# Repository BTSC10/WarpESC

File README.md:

# WarpESC
An open source 2 channel 50A ESC designed for a 2-4S LiPo Battery.
The design utilises a STM32F303 and 6 SIC634CD-T1-GE3 power stages to produce the 3 phase voltages.

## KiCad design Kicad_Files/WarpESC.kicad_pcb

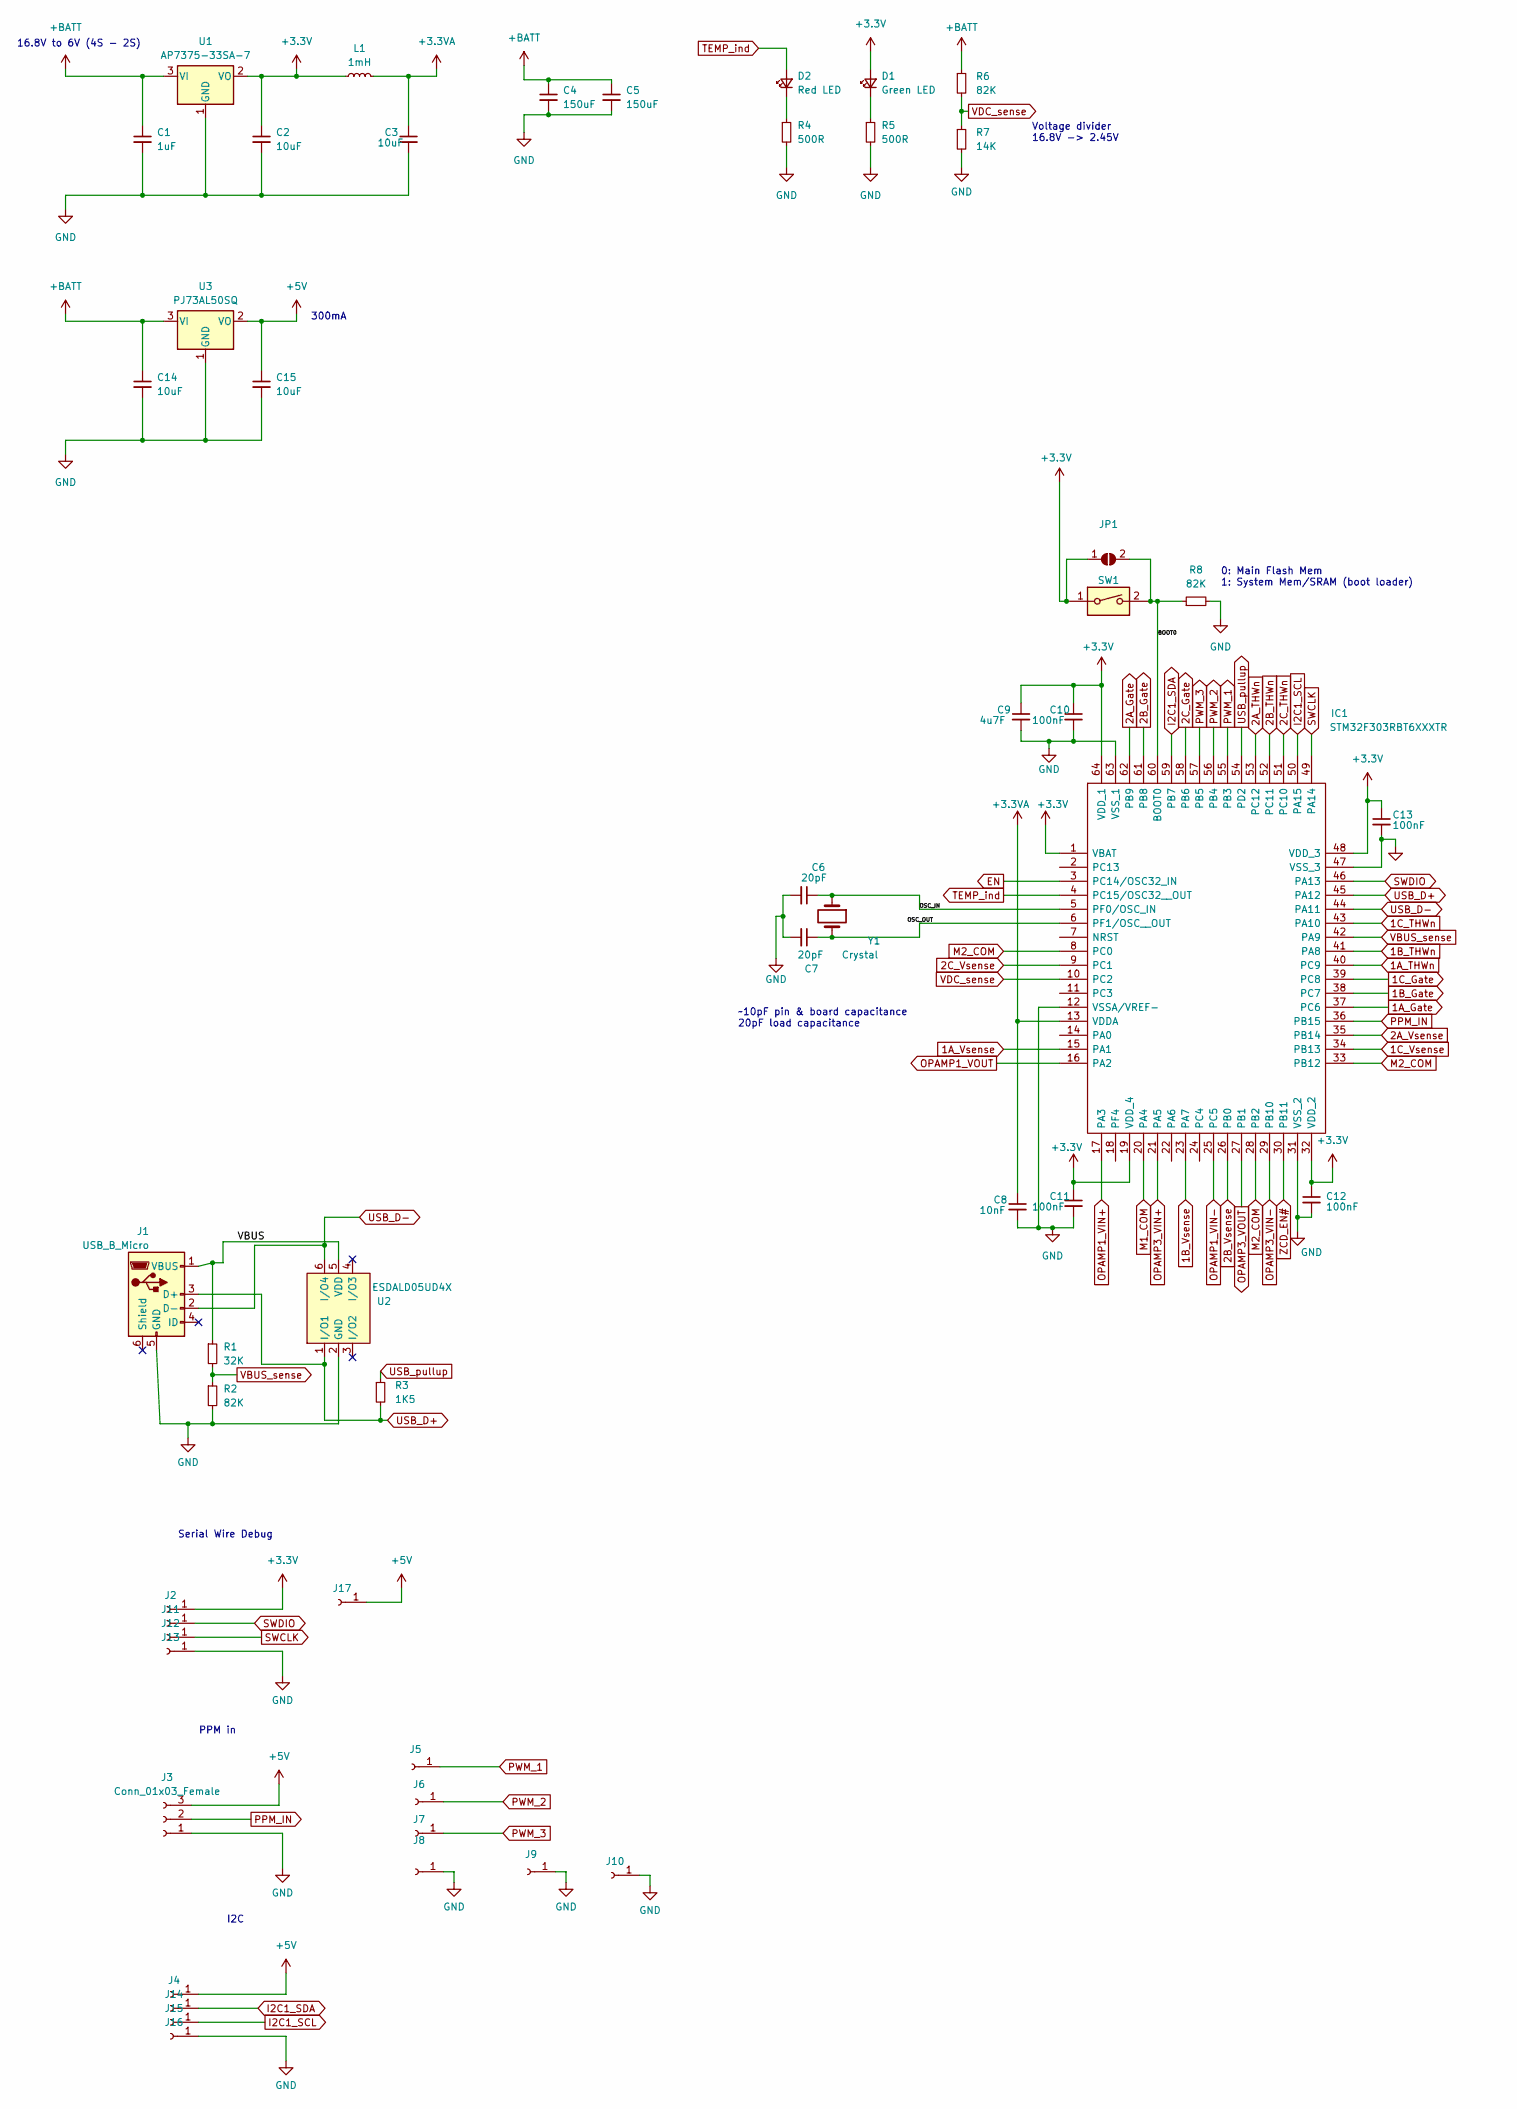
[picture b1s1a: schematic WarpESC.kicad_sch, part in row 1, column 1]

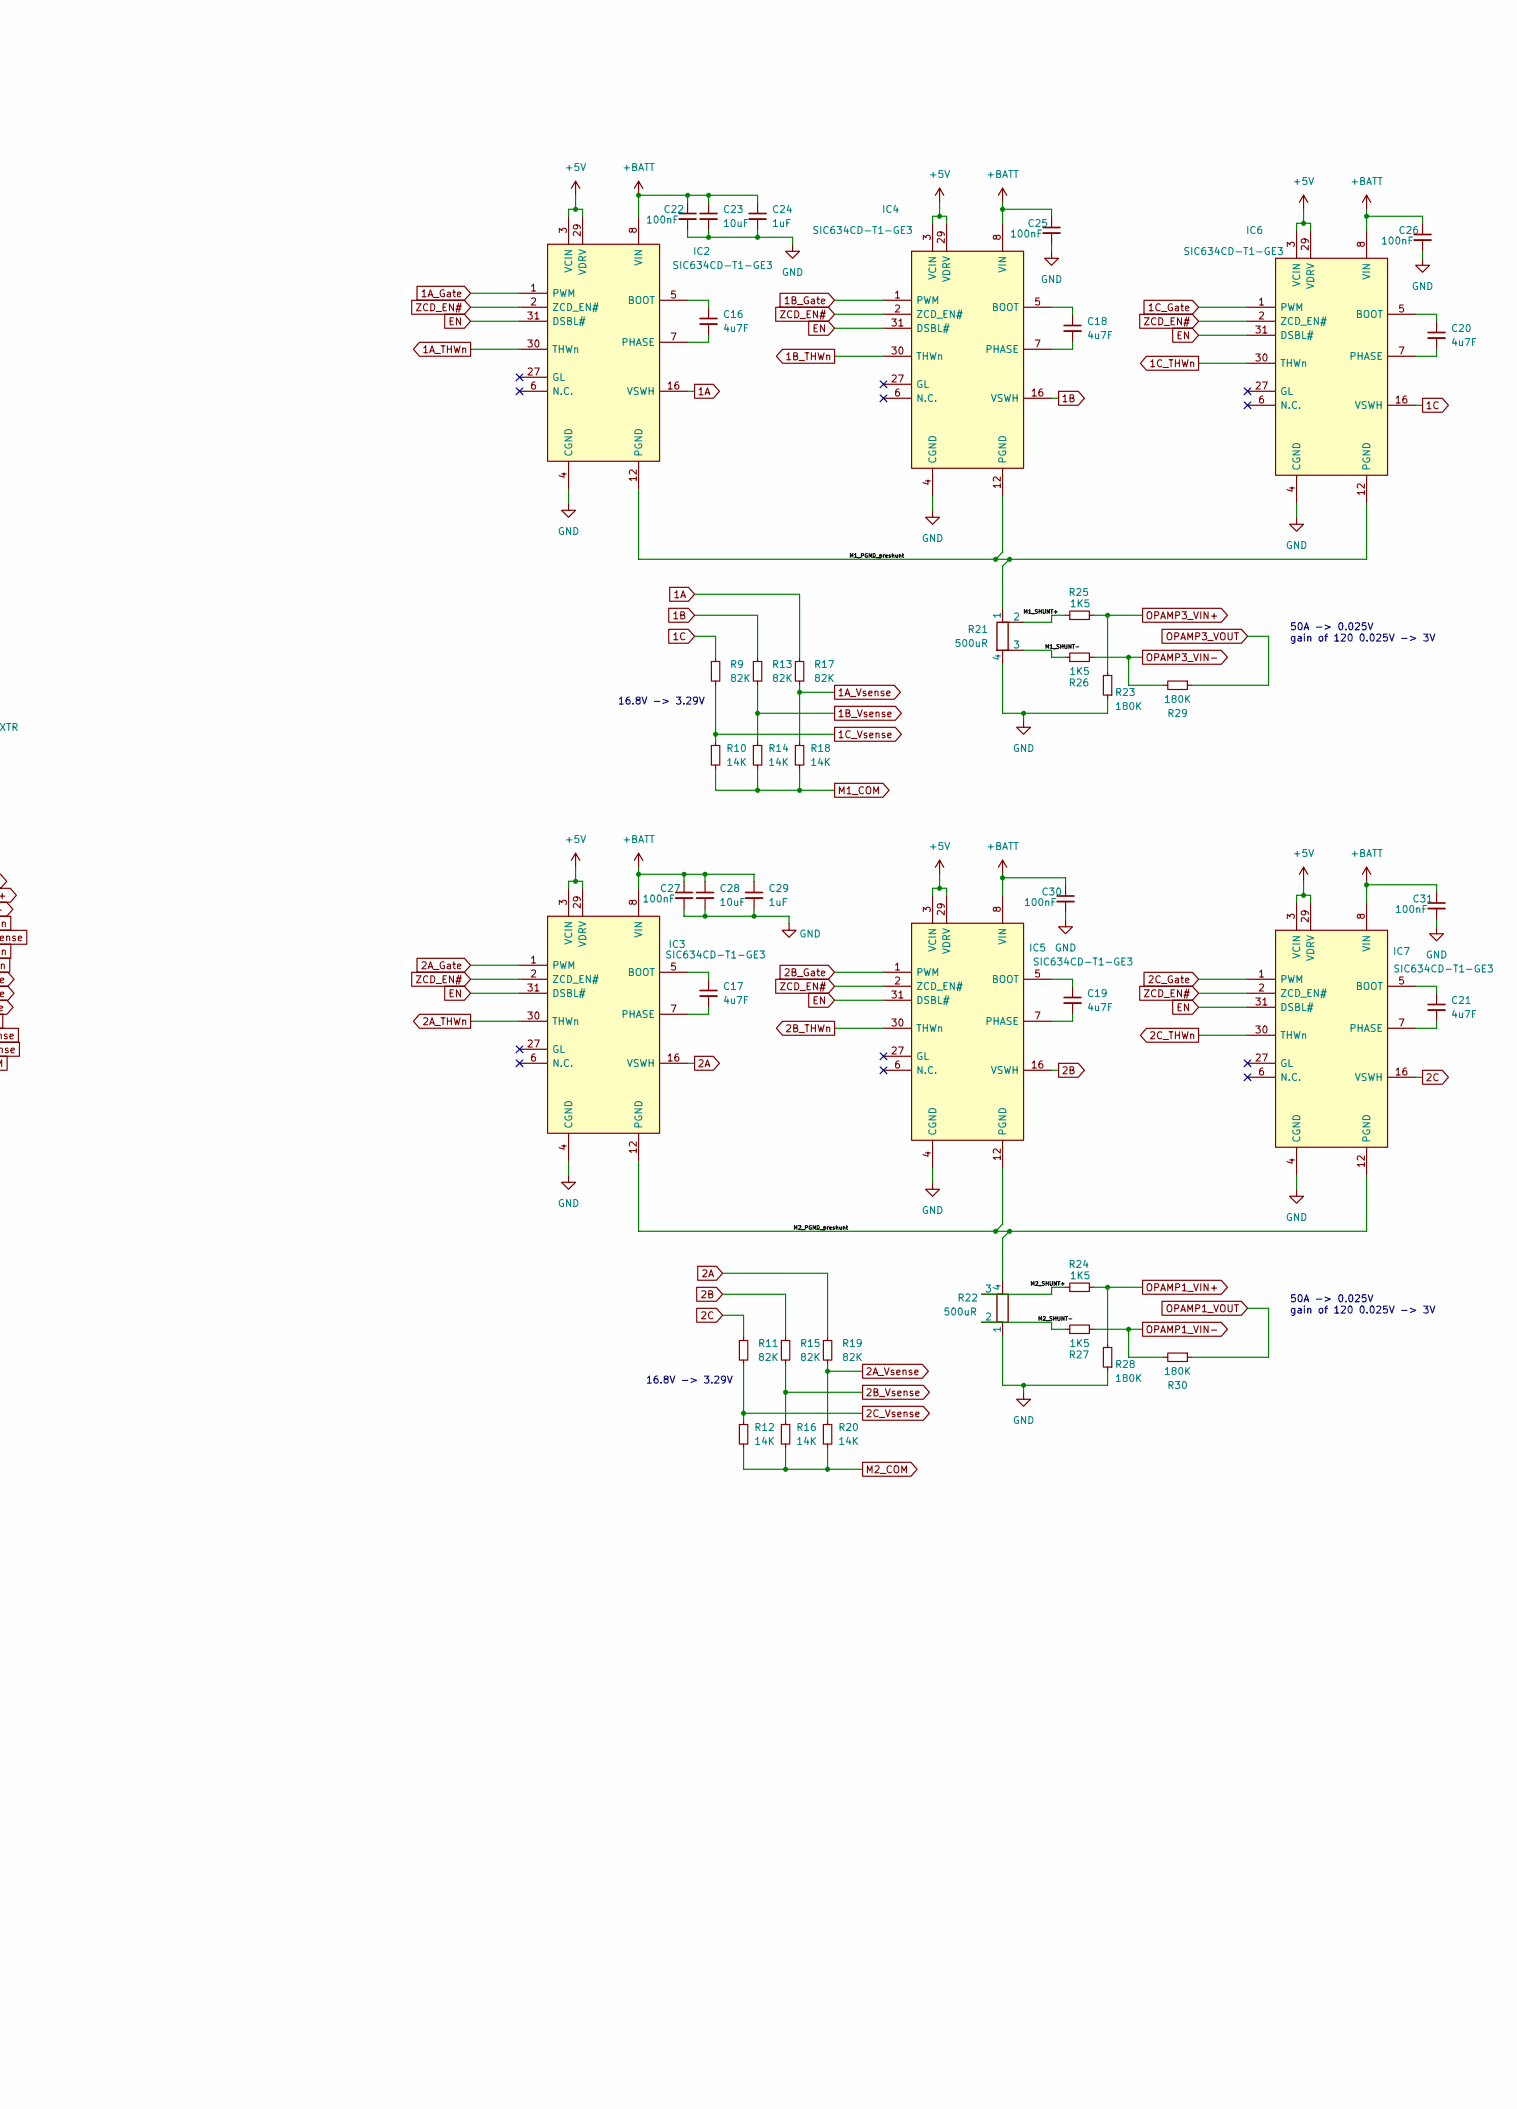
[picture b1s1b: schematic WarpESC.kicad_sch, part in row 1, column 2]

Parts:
C1, C24, C29: 1uF; C_0805_2012Metric
C2, C3, C15: 10uF; C_0402_1005Metric
C4, C5: 150uF
C6, C7: 20pF; C_0402_1005Metric
C8: 10nF; C_0402_1005Metric
C9: 4u7F; C_0603_1608Metric
C10, C11, C12, C13, C22, C25, C26, C27, C30, C31: 100nF; C_0402_1005Metric
C14, C23, C28: 10uF; C_1206_3216Metric
C16, C17, C18, C19, C20, C21: 4u7F; C_0402_1005Metric
D1: Green LED; LED_0603_1608Metric
D2: Red LED; LED_0603_1608Metric
IC1: STM32F303RBT6XXXTR; LQFP-64_10x10mm_P0.5mm; Manufacturer_Part_Number STM32F303RBT6XXXTR
IC2, IC3, IC4, IC5, IC6, IC7: SIC634CD-T1-GE3; SIC634CDT1GE3; Manufacturer_Part_Number SIC634CD-T1-GE3; Mouser Part Number 78-SIC634CD-T1-GE3
J1: USB_B_Micro; USB-MR-D-015
J2, J4, J5, J6, J7, J8, J9, J10, J12, J13, J15, J16, J17: Conn_01x01_Female; SolderWirePad_1x01_SMD_1x2mm
J3: Conn_01x03_Female; PinHeader_1x03_P2.54mm_Vertical
J11, J14: VV; SolderWirePad_1x01_SMD_1x2mm
JP1: SolderJumper_2_Open; SolderJumper-2_P1.3mm_Open_RoundedPad1.0x1.5mm
L1: 1mH; L_1210_3225Metric
R1: 32K; R_0402_1005Metric
R2, R6, R8, R9, R11, R13, R15, R17, R19: 82K; R_0402_1005Metric
R3, R24, R25, R26, R27: 1K5; R_0402_1005Metric
R4, R5: 500R; R_0805_2012Metric
R7, R10, R12, R14, R16, R18, R20: 14K; R_0402_1005Metric
R21, R22: 500uR; WSK12161L000FEA
R23, R28, R29, R30: 180K; R_0402_1005Metric
SW1: DS04-254-2-01BK-SMT; DS04-254-SMT
U1: AP7375-33SA-7; SOT-23
U2: ESDALD05UD4X; SOT-23-6
U3: PJ73AL50SQ; SOT-89-3
Y1: Crystal; Crystal_SMD_3225-4Pin_3.2x2.5mm

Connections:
1A: IC2.16 (VSWH), R17.1
1A_Gate: IC1.37 (PC6), IC2.1 (PWM)
1A_THWn: IC1.40 (PC9), IC2.30 (THWn)
1A_Vsense: IC1.15 (PA1), R17.2, R18.1
1B: IC4.16 (VSWH), R13.1
1B_Gate: IC1.38 (PC7), IC4.1 (PWM)
1B_THWn: IC1.41 (PA8), IC4.30 (THWn)
1B_Vsense: IC1.23 (PA7), R13.2, R14.1
1C: IC6.16 (VSWH), R9.1
1C_Gate: IC1.39 (PC8), IC6.1 (PWM)
1C_THWn: IC1.43 (PA10), IC6.30 (THWn)
1C_Vsense: IC1.34 (PB13), R9.2, R10.1
2A: IC3.16 (VSWH), R19.1
2A_Gate: IC1.62 (PB9), IC3.1 (PWM)
2A_THWn: IC1.53 (PC12), IC3.30 (THWn)
2A_Vsense: IC1.35 (PB14), R19.2, R20.1
2B: IC5.16 (VSWH), R15.1
2B_Gate: IC1.61 (PB8), IC5.1 (PWM)
2B_THWn: IC1.52 (PC11), IC5.30 (THWn)
2B_Vsense: IC1.26 (PB0), R15.2, R16.1
2C: IC7.16 (VSWH), R11.1
2C_Gate: IC1.58 (PB6), IC7.1 (PWM)
2C_THWn: IC1.51 (PC10), IC7.30 (THWn)
2C_Vsense: IC1.9 (PC1), R11.2, R12.1
+3.3VA: C3.1, C8.1, IC1.13 (VDDA), L1.2
+3V3: C2.1, C9.1, C10.1, C11.1, C12.1, C13.1, D1.2 (A), IC1.1 (VBAT), IC1.19 (VDD_4), IC1.32 (VDD_2), IC1.48 (VDD_3), IC1.64 (VDD_1), J2.1, JP1.1 (A), L1.1, SW1.1, U1.2 (VO)
+5V: C15.1, IC2.3 (VCIN), IC2.29 (VDRV), IC3.3 (VCIN), IC3.29 (VDRV), IC4.3 (VCIN), IC4.29 (VDRV), IC5.3 (VCIN), IC5.29 (VDRV), IC6.3 (VCIN), IC6.29 (VDRV), IC7.3 (VCIN), IC7.29 (VDRV), J3.3, J4.1, J17.1, U3.2 (VO)
+BATT: C1.1, C4.1, C5.1, C14.1, C22.1, C23.1, C24.1, C25.1, C26.1, C27.1, C28.1, C29.1, C30.1, C31.1, IC2.8 (VIN), IC3.8 (VIN), IC4.8 (VIN), IC5.8 (VIN), IC6.8 (VIN), IC7.8 (VIN), R6.1, U1.3 (VI), U3.3 (VI)
/BOOT0: IC1.60 (BOOT0), JP1.2 (B), R8.1, SW1.2
/M1_PGND_preshunt: IC2.12 (PGND), IC4.12 (PGND), IC6.12 (PGND), R21.1
/M1_SHUNT+: R21.2, R25.1
/M1_SHUNT-: R21.3, R26.1
/M2_PGND_preshunt: IC3.12 (PGND), IC5.12 (PGND), IC7.12 (PGND), R22.4
/M2_SHUNT+: R22.3, R24.1
/M2_SHUNT-: R22.2, R27.1
/OSC_IN: C6.1, IC1.5 (PF0/OSC_IN), Y1.1
/OSC_OUT: C7.1, IC1.6 (PF1/OSC__OUT), Y1.3
/VBUS: J1.1 (VBUS), R1.1, U2.5 (VDD)
EN: IC1.3 (PC14/OSC32_IN), IC2.31 (DSBL#), IC3.31 (DSBL#), IC4.31 (DSBL#), IC5.31 (DSBL#), IC6.31 (DSBL#), IC7.31 (DSBL#)
GND: C1.2, C2.2, C3.2, C4.2, C5.2, C6.2, C7.2, C8.2, C9.2, C10.2, C11.2, C12.2, C13.2, C14.2, C15.2, C22.2, C23.2, C24.2, C25.2, C26.2, C27.2, C28.2, C29.2, C30.2, C31.2, IC1.12 (VSSA/VREF-), IC1.31 (VSS_2), IC1.47 (VSS_3), IC1.63 (VSS_1), IC2.4 (CGND), IC3.4 (CGND), IC4.4 (CGND), IC5.4 (CGND), IC6.4 (CGND), IC7.4 (CGND), J1.5 (GND), J3.1, J8.1, J9.1, J10.1, J13.1, J16.1, R2.2, R4.2, R5.2, R7.2, R8.2, R21.4, R22.1, R23.1, R28.1, U1.1 (GND), U2.2 (GND), U3.1 (GND)
I2C1_SCL: IC1.50 (PA15), J15.1
I2C1_SDA: IC1.59 (PB7), J14.1
M1_COM: IC1.20 (PA4), R10.2, R14.2, R18.2
M2_COM: IC1.8 (PC0), IC1.28 (PB2), IC1.33 (PB12), R12.2, R16.2, R20.2
unnamed: C16.1, IC2.5 (BOOT)
unnamed: C16.2, IC2.7 (PHASE)
unnamed: C17.1, IC3.5 (BOOT)
unnamed: C17.2, IC3.7 (PHASE)
unnamed: C18.1, IC4.5 (BOOT)
unnamed: C18.2, IC4.7 (PHASE)
unnamed: C19.1, IC5.5 (BOOT)
unnamed: C19.2, IC5.7 (PHASE)
unnamed: C20.1, IC6.5 (BOOT)
unnamed: C20.2, IC6.7 (PHASE)
unnamed: C21.1, IC7.5 (BOOT)
unnamed: C21.2, IC7.7 (PHASE)
unnamed: D1.1 (K), R5.1
unnamed: D2.1 (K), R4.1
OPAMP1_VIN+: IC1.17 (PA3), R24.2, R28.2
OPAMP1_VIN-: IC1.25 (PC5), R27.2, R30.2
OPAMP1_VOUT: IC1.16 (PA2), R30.1
OPAMP3_VIN+: IC1.21 (PA5), R23.2, R25.2
OPAMP3_VIN-: IC1.29 (PB10), R26.2, R29.2
OPAMP3_VOUT: IC1.27 (PB1), R29.1
PPM_IN: IC1.36 (PB15), J3.2
PWM_1: IC1.55 (PB3), J5.1
PWM_2: IC1.56 (PB4), J6.1
PWM_3: IC1.57 (PB5), J7.1
SWCLK: IC1.49 (PA14), J12.1
SWDIO: IC1.46 (PA13), J11.1
TEMP_ind: D2.2 (A), IC1.4 (PC15/OSC32__OUT)
USB_D+: IC1.45 (PA12), J1.3 (D+), R3.2, U2.1 (I/O1)
USB_D-: IC1.44 (PA11), J1.2 (D-), U2.6 (I/O4)
USB_pullup: IC1.54 (PD2), R3.1
VBUS_sense: IC1.42 (PA9), R1.2, R2.1
VDC_sense: IC1.10 (PC2), R6.2, R7.1
ZCD_EN#: IC1.30 (PB11), IC2.2 (ZCD_EN#), IC3.2 (ZCD_EN#), IC4.2 (ZCD_EN#), IC5.2 (ZCD_EN#), IC6.2 (ZCD_EN#), IC7.2 (ZCD_EN#)

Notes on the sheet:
Serial Wire Debug
16.8V -> 3.29V
16.8V to 6V (4S - 2S)
50A -> 0.025V gain of 120 0.025V -> 3V
0: Main Flash Mem 1: System Mem/SRAM (boot loader)
300mA
~10pF pin & board capacitance 20pF load capacitance
PPM in
I2C
Voltage divider 16.8V -> 2.45V

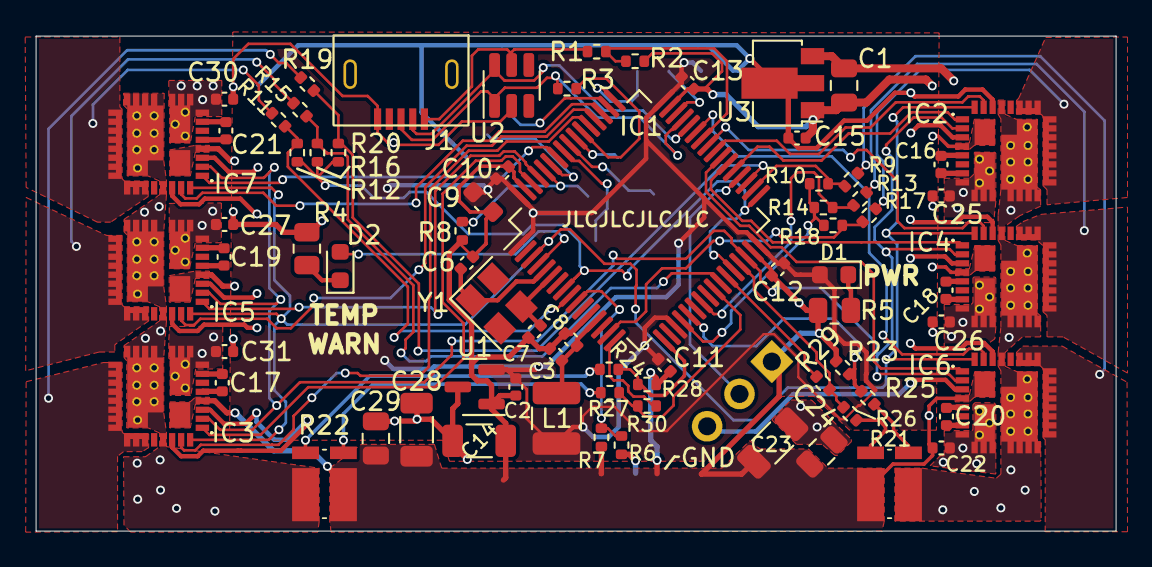
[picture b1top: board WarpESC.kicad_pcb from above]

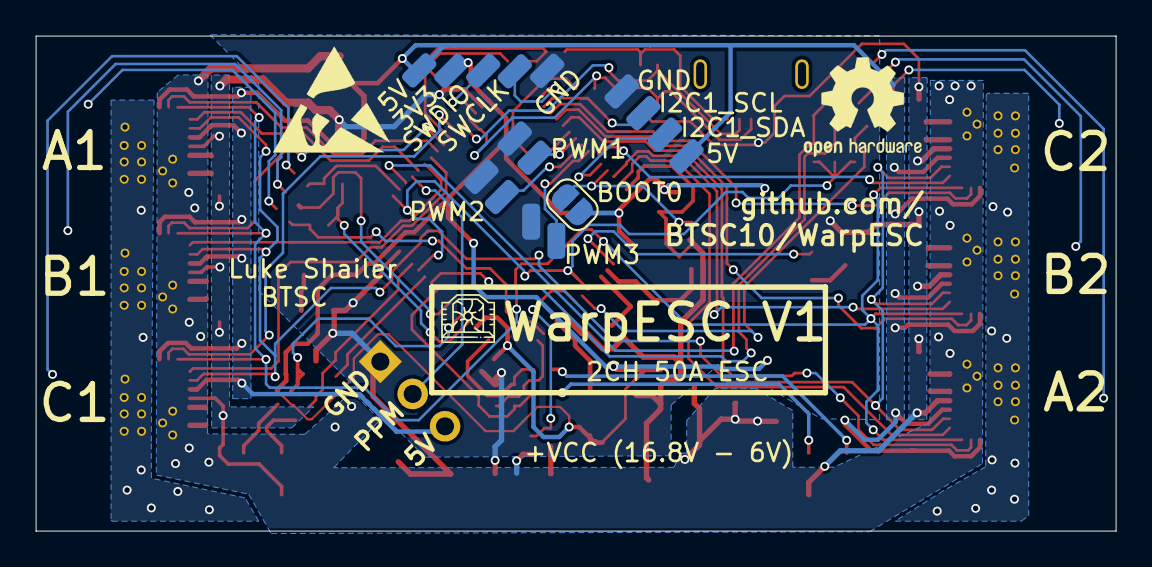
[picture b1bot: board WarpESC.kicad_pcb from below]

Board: 2 copper layers, 60.0 x 27.5 mm, 91 parts (16 on the bottom side), 77 nets.

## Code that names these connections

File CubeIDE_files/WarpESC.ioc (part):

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Mcu.Name=STM32F303R(B-C)Tx
Mcu.Package=LQFP64
Mcu.UserName=STM32F303RBTx
PA1.Signal=SharedAnalog_PA1
PA10.GPIOParameters=GPIO_Label
PA10.GPIO_Label=C1_THWn
PA10.Signal=GPIO_Input
PA11.Mode=Device
PA11.Signal=USB_DM
PA12.Mode=Device
PA12.Signal=USB_DP
PA13.Mode=Serial_Wire
PA13.Signal=SYS_JTMS-SWDIO
PA14.Mode=Serial_Wire
PA14.Signal=SYS_JTCK-SWCLK
PA15.Mode=I2C
PA15.Signal=I2C1_SCL
PA2.Signal=SharedAnalog_PA2
PA3.Mode=Standalone
PA3.Signal=OPAMP1_VINP
PA4.Signal=SharedAnalog_PA4
PA5.Mode=Standalone
PA5.Signal=OPAMP3_VINP
PA7.Signal=SharedAnalog_PA7
PA8.GPIOParameters=GPIO_Label
PA8.GPIO_Label=B1_THWn
PA8.Signal=GPIO_Input
PB0.Signal=SharedAnalog_PB0
PB1.Signal=SharedAnalog_PB1
PB10.Mode=Standalone
PB10.Signal=OPAMP3_VINM
PB11.Signal=GPIO_Output
PB12.Mode=INM
PB12.Signal=COMP3_INM
PB13.Signal=SharedAnalog_PB13
PB14.Signal=SharedAnalog_PB14
PB15.GPIOParameters=GPIO_Label
PB15.GPIO_Label=PPM_IN
PB15.Signal=GPIO_Input
PB2.Mode=INM
PB2.Signal=COMP4_INM
PB3.GPIOParameters=GPIO_Label
PB3.GPIO_Label=PWM1
PB3.Signal=GPIO_Input
PB4.GPIOParameters=GPIO_Label
PB4.GPIO_Label=PWM2
PB4.Signal=GPIO_Input
PB5.GPIOParameters=GPIO_Label
PB5.GPIO_Label=PWM3
PB5.Signal=GPIO_Output
PB6.Signal=S_TIM8_CH1
PB7.Mode=I2C
PB7.Signal=I2C1_SDA
PB8.Signal=S_TIM8_CH2
PB9.Signal=S_TIM8_CH3
PC0.Mode=INM
PC0.Signal=COMP7_INM
PC1.Mode=INP
PC1.Signal=COMP7_INP
PC10.GPIOParameters=GPIO_Label
PC10.GPIO_Label=C2_THWn
PC10.Signal=GPIO_Input
PC11.GPIOParameters=GPIO_Label
PC11.GPIO_Label=B2_THWn
PC11.Signal=GPIO_Input
PC12.GPIOParameters=GPIO_Label
PC12.GPIO_Label=A2_THWn
PC12.Signal=GPIO_Input
PC14-OSC32_IN.GPIOParameters=GPIO_Label
PC14-OSC32_IN.GPIO_Label=EN
PC14-OSC32_IN.Signal=GPIO_Output
PC15-OSC32_OUT.GPIOParameters=GPIO_Label
PC15-OSC32_OUT.GPIO_Label=TEMP_ind
PC15-OSC32_OUT.Signal=GPIO_Output
PC2.Signal=ADCx_IN8
PC5.Mode=Standalone
PC5.Signal=OPAMP1_VINM
PC6.Signal=S_TIM3_CH1
PC7.Signal=S_TIM3_CH2
PC8.Signal=S_TIM3_CH3
PC9.GPIOParameters=GPIO_Label
PC9.GPIO_Label=A1_THWn
PC9.Signal=GPIO_Input
PD2.GPIOParameters=GPIO_Label
PD2.GPIO_Label=USB_pullup
PD2.Signal=GPIO_Output
PF0-OSC_IN.Mode=HSE-External-Oscillator
PF0-OSC_IN.Signal=RCC_OSC_IN
PF1-OSC_OUT.Mode=HSE-External-Oscillator
PF1-OSC_OUT.Signal=RCC_OSC_OUT
RCC.HSEPLLFreq_Value=8000000
RCC.HSE_VALUE=8000000
RCC.SYSCLKFreq_VALUE=8000000
board=custom

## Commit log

2022-10-20 Create x
2022-10-20 Add gerber and kicad files
2022-10-20 Uploading first CubeIDE files
    Only contains pinout for the stm32
2022-10-20 Initial CubeIDE files
    Doesn't contain any code, just the pinout for the stm32
